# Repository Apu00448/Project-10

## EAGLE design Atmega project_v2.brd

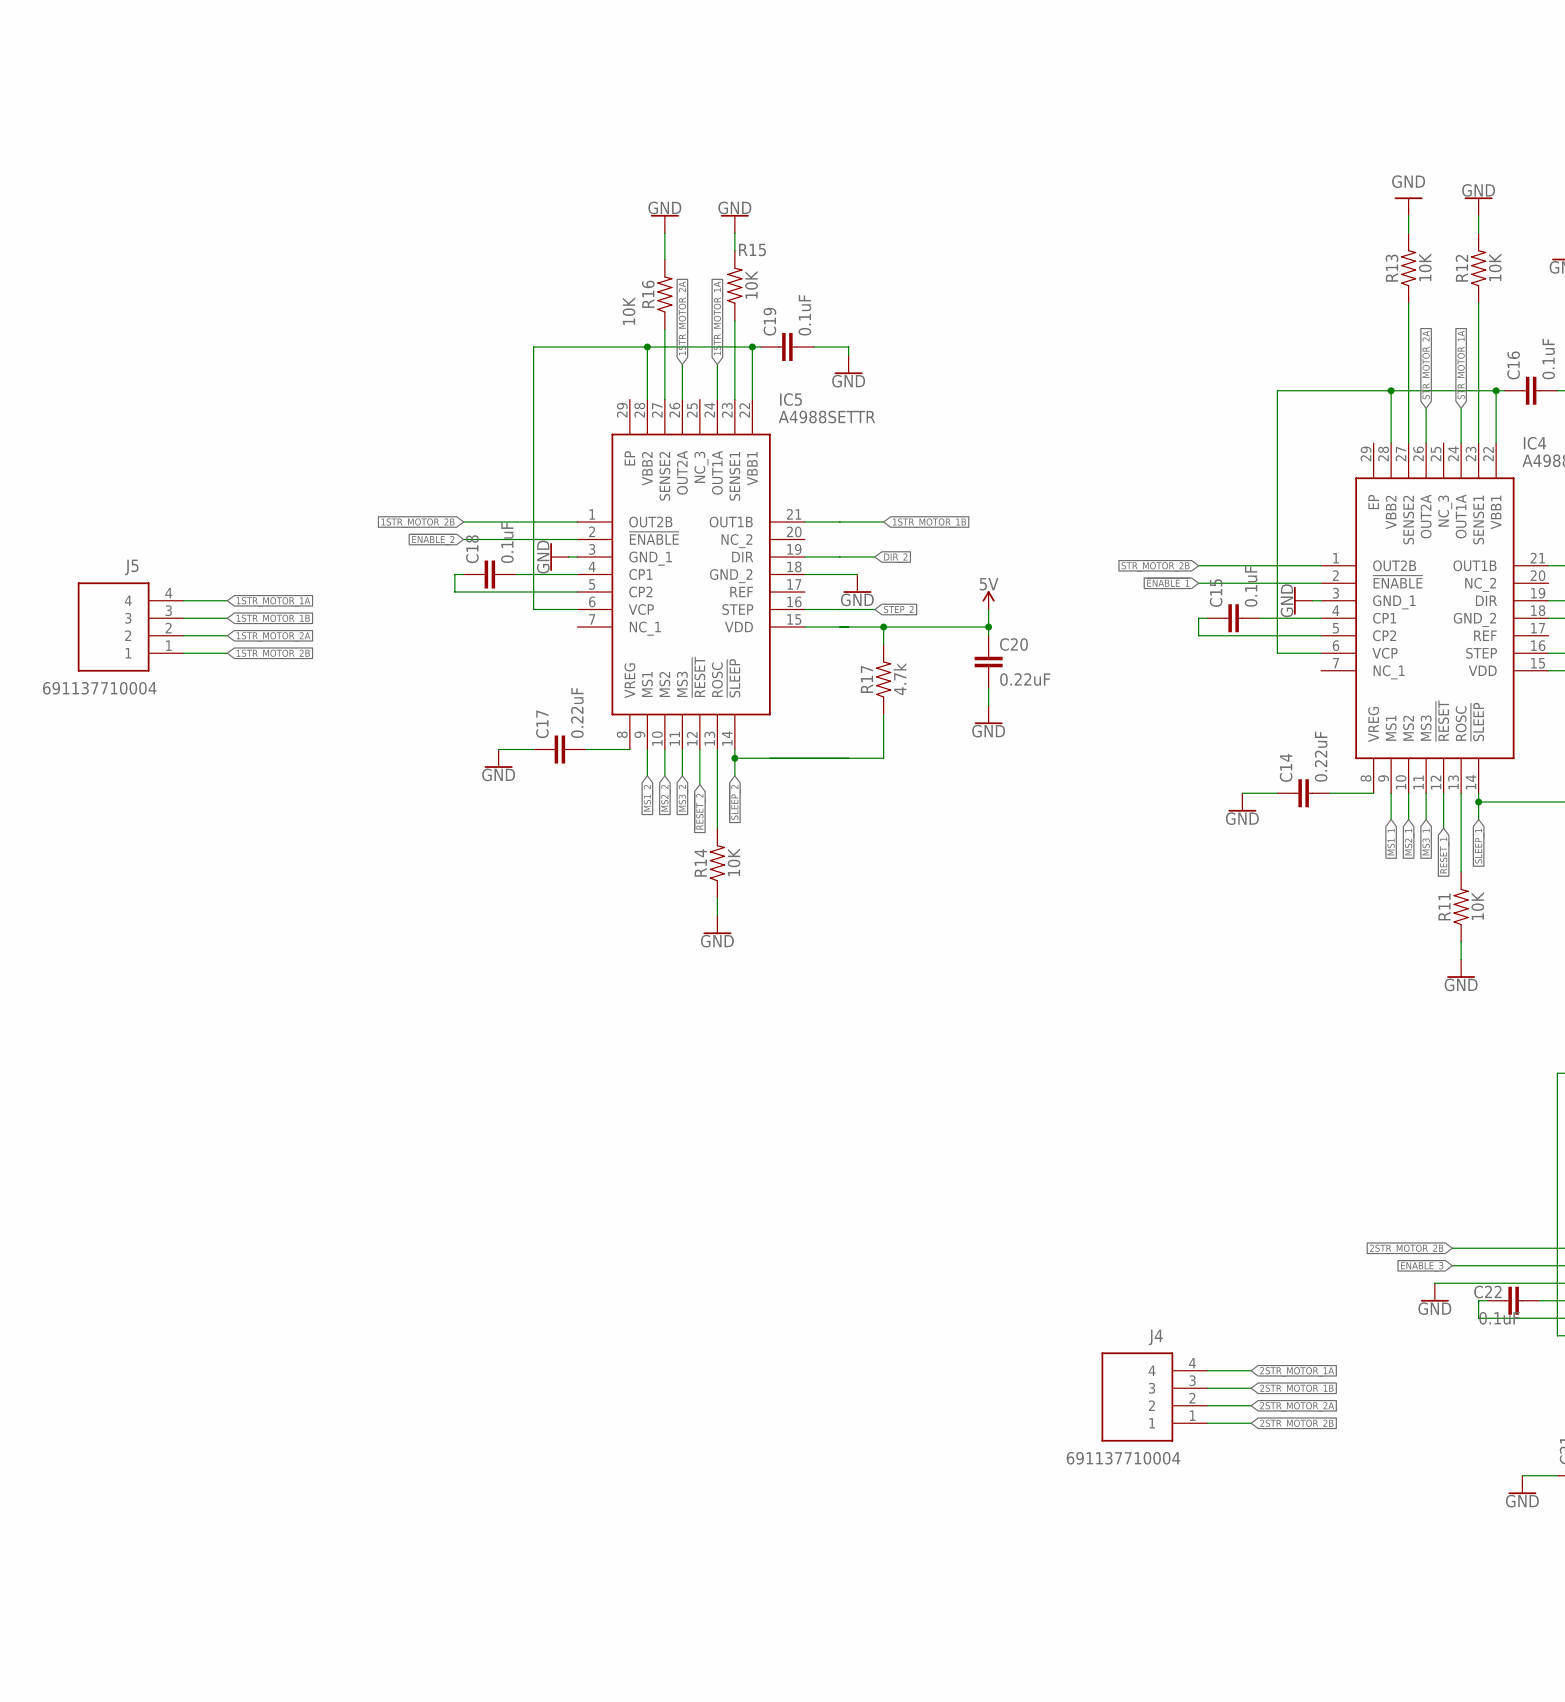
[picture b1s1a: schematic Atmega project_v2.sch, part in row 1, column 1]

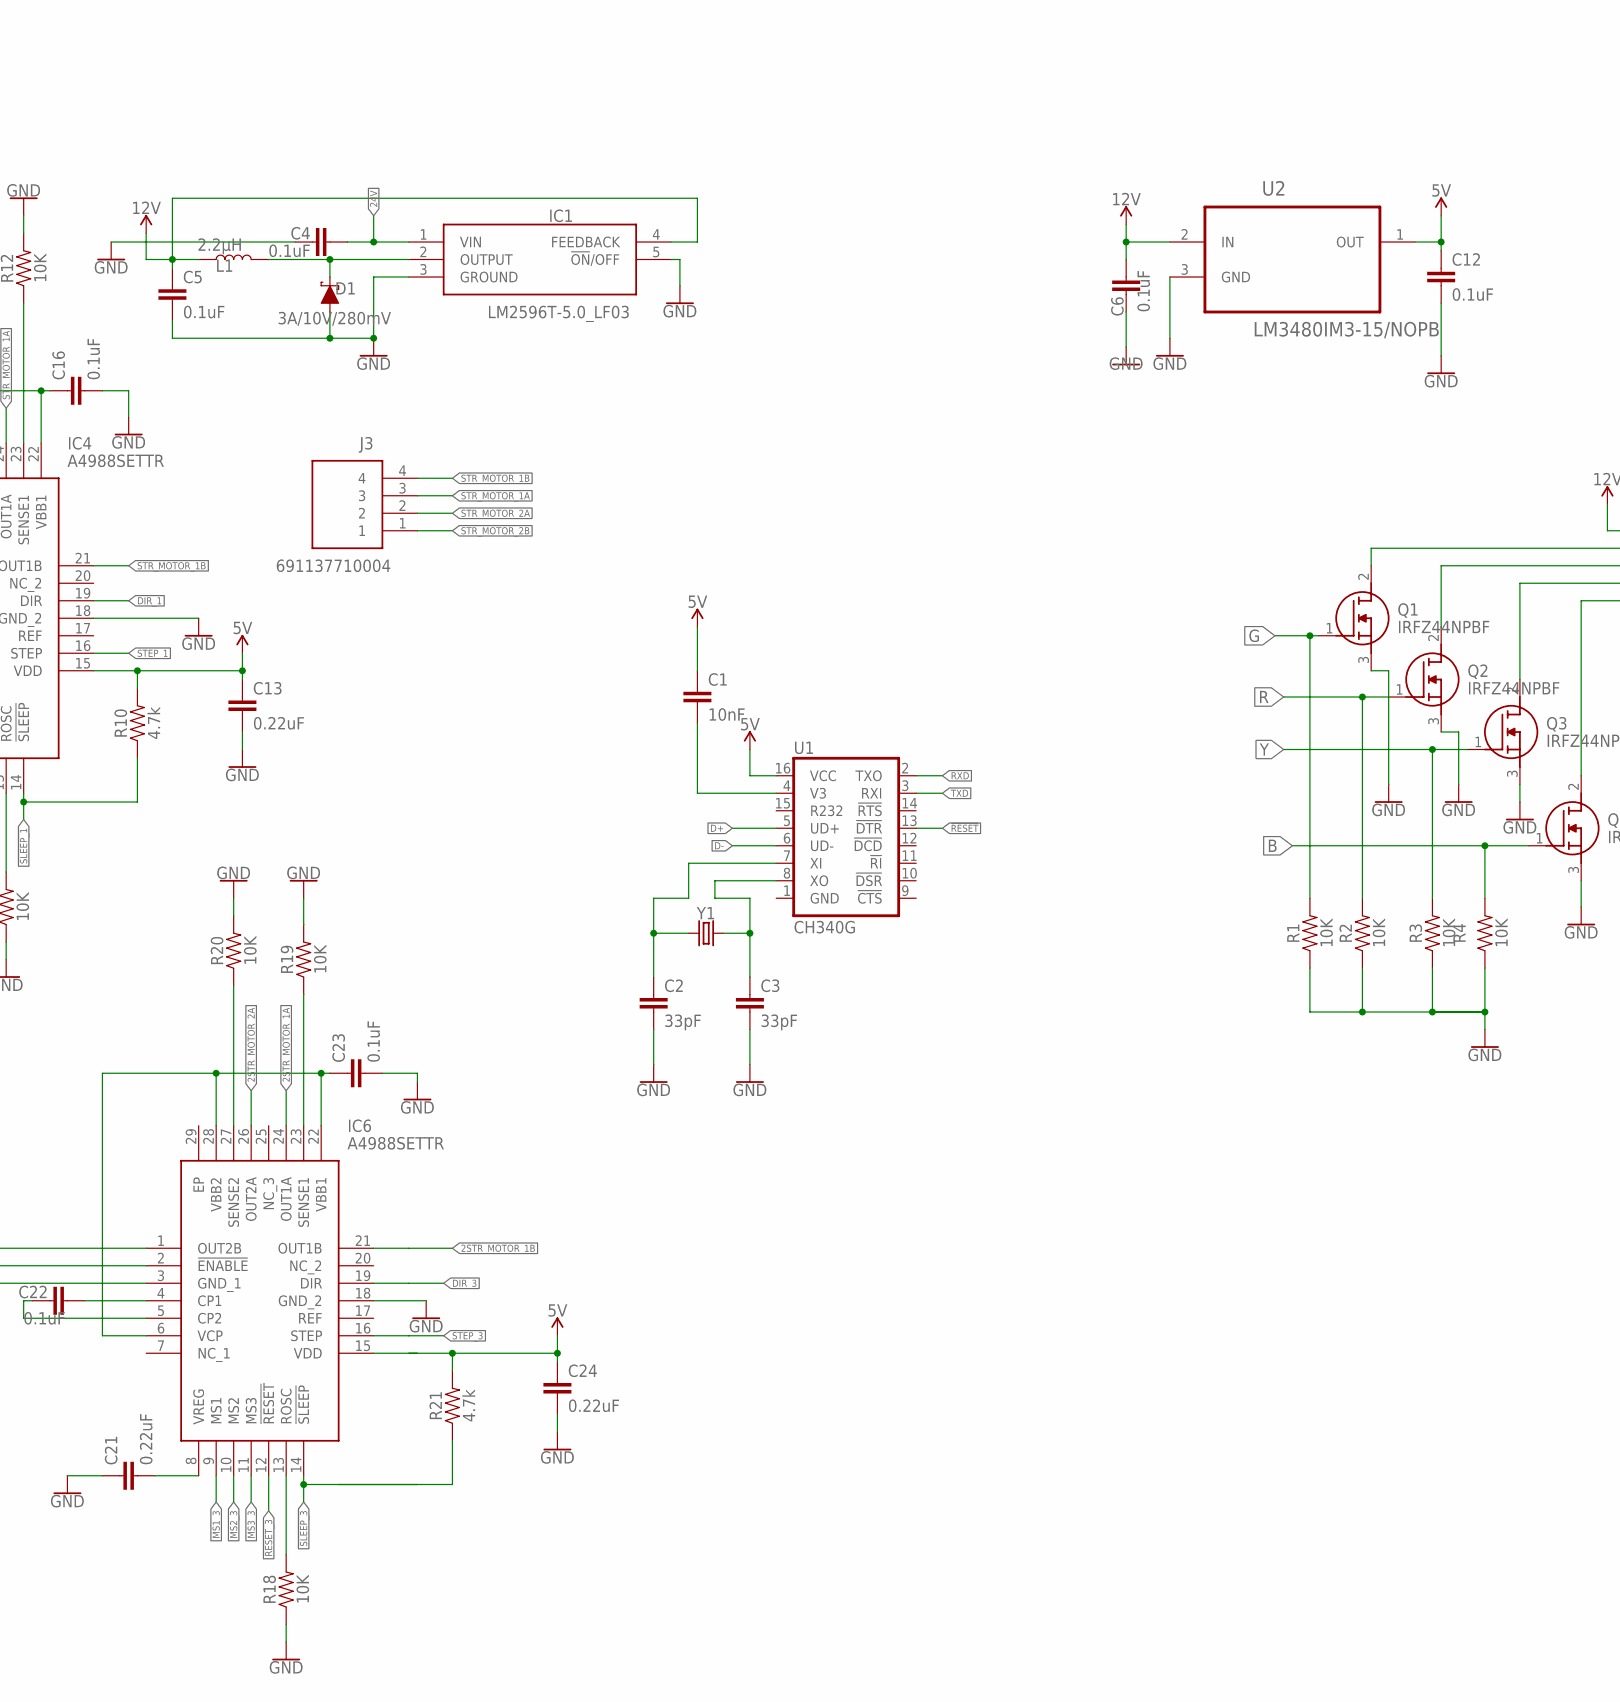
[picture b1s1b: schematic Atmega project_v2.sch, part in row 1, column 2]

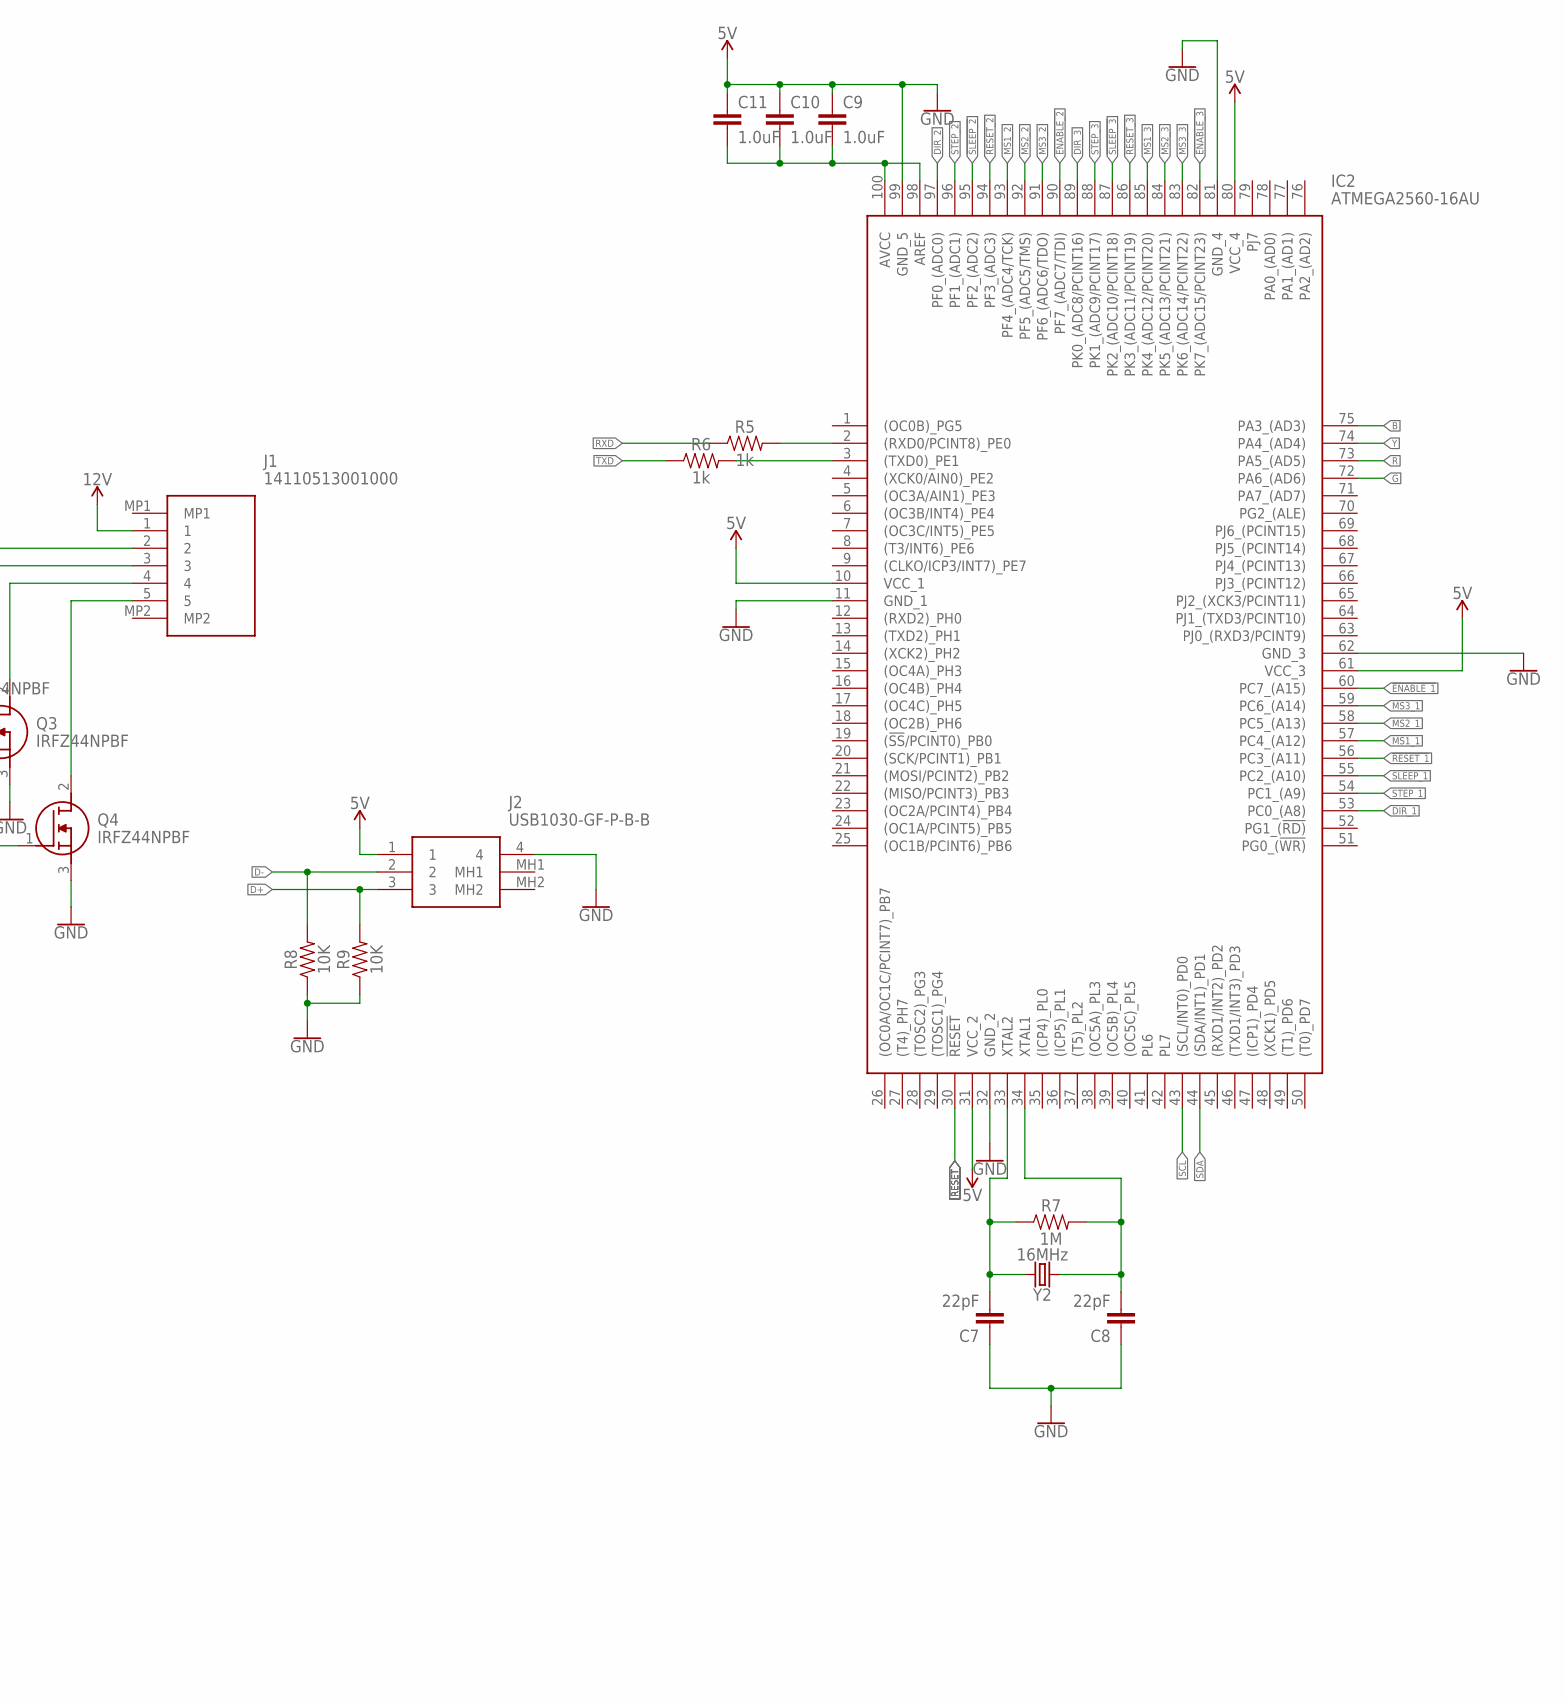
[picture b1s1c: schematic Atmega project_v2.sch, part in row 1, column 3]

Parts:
C1: 10nF; 0402-TIGHT
C2, C3: 33pF; 0402-TIGHT
C4: 0.1uF; 0603
C5, C6, C12, C15, C16, C18, C19, C22, C23: 0.1uF; 0402-TIGHT
C7, C8: 22pF; 0402-TIGHT
C9, C10, C11: 1.0uF; 0402-TIGHT
C13, C14, C17, C20, C21, C24: 0.22uF; 0402-TIGHT
D1: 3A/10V/280mV; SOD-323
IC1: LM2596T-5.0_LF03; TO170P470X1028X2142-5P
IC2: ATMEGA2560-16AU; QFP50P1600X1600X120-100N
IC4, IC5, IC6: A4988SETTR; QFN50P500X500X100-29N
J1: 14110513001000
J2: USB1030-GF-P-B-B; USB1030GFPBB
J3, J4, J5: 691137710004
L1: 2.2μH; 0805-WIDE
Q1, Q2, Q3, Q4: IRFZ44NPBF; TO254P483X1016X1994-3P
R1, R2, R3, R4, R8, R9, R11, R12, R13, R14, R15, R16, R18, R19, R20: 10K; 0402-TIGHT
R5, R6: 1k; 0402-TIGHT
R7: 1M; 0402-TIGHT
R10, R17, R21: 4.7k; 0402-TIGHT
U1: CH340G; SO016
U2: LM3480IM3-15/NOPB; SOT95P251X112-3N
Y1: CRYSTAL-12MHZ; CRYSTAL-SMD-2X2.5MM
Y2: 16MHz; CRYSTAL-SMD-5X3.2-4PAD

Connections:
1STR_MOTOR_1A: IC5.24 (OUT1A), J5.4
1STR_MOTOR_1B: J5.3
1STR_MOTOR_2A: IC5.26 (OUT2A), J5.2
1STR_MOTOR_2B: IC5.1 (OUT2B), J5.1
2STR_MOTOR_1A: IC6.24 (OUT1A), J4.4
2STR_MOTOR_1B: J4.3
2STR_MOTOR_2A: IC6.26 (OUT2A), J4.2
2STR_MOTOR_2B: IC6.1 (OUT2B), J4.1
5V: C1.1, C9.1, C10.1, C11.1, C12.1, C13.1, C20.1, C24.1, IC2.10 (VCC_1), IC2.31 (VCC_2), IC2.61 (VCC_3), IC2.80 (VCC_4), IC2.99 (GND_5), IC4.15 (VDD), J2.1, R10.2, R17.2, R21.2, U1.16 (VCC), U2.1 (OUT)
5V1: IC5.15 (VDD)
5V2: IC6.15 (VDD)
12V: C5.1, C6.2, IC1.4 (FEEDBACK), J1.1, L1.1, U2.2 (IN)
24V: C4.2, IC1.1 (VIN)
!ENABLE_1: IC2.60 (PC7_(A15)), IC4.2 (!ENABLE)
!ENABLE_2: IC2.90 (PF7_(ADC7/TDI)), IC5.2 (!ENABLE)
!ENABLE_3: IC2.82 (PK7_(ADC15/PCINT23)), IC6.2 (!ENABLE)
!RESET: IC2.30 (!RESET), U1.13 (!DTR)
!RESET_1: IC2.56 (PC3_(A11)), IC4.12 (!RESET)
!RESET_2: IC2.94 (PF3_(ADC3)), IC5.12 (!RESET)
!RESET_3: IC2.86 (PK3_(ADC11/PCINT19)), IC6.12 (!RESET)
!SLEEP_1: IC2.55 (PC2_(A10)), IC4.14 (!SLEEP), R10.1
!SLEEP_2: IC2.95 (PF2_(ADC2)), IC5.14 (!SLEEP), R17.1, R21.1
!SLEEP_3: IC2.87 (PK2_(ADC10/PCINT18)), IC6.14 (!SLEEP)
B: IC2.75 (PA3_(AD3)), Q4.1 (G), R4.2
D+: J2.3, R9.2, U1.5 (UD+)
D-: J2.2, R8.2, U1.6 (UD-)
DIR_1: IC2.53 (PC0_(A8)), IC4.19 (DIR)
DIR_2: IC2.97 (PF0_(ADC0)), IC5.19 (DIR), IC6.19 (DIR)
DIR_3: IC2.89 (PK0_(ADC8/PCINT16))
G: IC2.72 (PA6_(AD6)), Q1.1 (G), R1.2
GND: C2.2, C3.2, C4.1, C5.2, C6.1, C7.1, C8.1, C12.2, C13.2, C14.1, C16.2, C17.1, C19.2, C20.2, C21.1, C23.2, C24.2, D1.A, IC1.3 (GROUND), IC1.5 (!ON!/OFF), IC2.11 (GND_1), IC2.32 (GND_2), IC2.62 (GND_3), IC2.81 (GND_4), IC4.3 (GND_1), IC4.18 (GND_2), IC5.3 (GND_1), IC5.18 (GND_2), IC6.3 (GND_1), IC6.18 (GND_2), J2.4, Q1.3 (S), Q2.3 (S), Q3.3 (S), Q4.3 (S), R1.1, R2.1, R3.1, R4.1, R8.1, R9.1, R11.1, R12.2, R13.2, R14.1, R15.2, R16.2, R18.1, R19.2, R20.2, U2.3 (GND)
MS1_1: IC2.57 (PC4_(A12)), IC4.9 (MS1)
MS1_2: IC2.93 (PF4_(ADC4/TCK)), IC5.9 (MS1)
MS1_3: IC2.85 (PK4_(ADC12/PCINT20)), IC6.9 (MS1)
MS2_1: IC2.58 (PC5_(A13)), IC4.10 (MS2)
MS2_2: IC2.92 (PF5_(ADC5/TMS)), IC5.10 (MS2)
MS2_3: IC2.84 (PK5_(ADC13/PCINT21)), IC6.10 (MS2)
MS3_1: IC2.59 (PC6_(A14)), IC4.11 (MS3)
MS3_2: IC2.91 (PF6_(ADC6/TDO)), IC5.11 (MS3)
MS3_3: IC2.83 (PK6_(ADC14/PCINT22)), IC6.11 (MS3)
unnamed: C1.2, U1.4 (V3)
unnamed: J1.2, Q1.2 (D)
unnamed: J1.3, Q2.2 (D)
unnamed: J1.4, Q3.2 (D)
unnamed: J1.5, Q4.2 (D)
unnamed: C2.1, U1.7 (XI), Y1.P1 (1)
unnamed: C3.1, U1.8 (XO), Y1.P3 (2)
unnamed: C8.2, IC2.34 (XTAL1), R7.2, Y2.1
unnamed: C7.2, IC2.33 (XTAL2), R7.1, Y2.3 (2)
unnamed: C9.2, C10.2, C11.2, IC2.98 (AREF), IC2.100 (AVCC)
unnamed: C14.2, IC4.8 (VREG)
unnamed: C15.2, IC4.4 (CP1)
unnamed: IC4.13 (ROSC), R11.2
unnamed: C15.1, IC4.5 (CP2)
unnamed: C16.1, IC4.6 (VCP), IC4.22 (VBB1), IC4.28 (VBB2)
unnamed: D1.C, IC1.2 (OUTPUT), L1.2
unnamed: C21.2, IC6.8 (VREG)
unnamed: IC6.13 (ROSC), R18.2
unnamed: IC4.23 (SENSE1), R12.1
unnamed: IC4.27 (SENSE2), R13.1
unnamed: C22.2, IC6.4 (CP1)
unnamed: C22.1, IC6.5 (CP2)
unnamed: C17.2, IC5.8 (VREG)
unnamed: IC5.13 (ROSC), R14.2
unnamed: C18.2, IC5.4 (CP1)
unnamed: C18.1, IC5.5 (CP2)
unnamed: C19.1, IC5.6 (VCP), IC5.22 (VBB1), IC5.28 (VBB2)
unnamed: IC5.23 (SENSE1), R15.1
unnamed: IC5.27 (SENSE2), R16.1
unnamed: C23.1, IC6.6 (VCP), IC6.22 (VBB1), IC6.28 (VBB2)
unnamed: IC6.23 (SENSE1), R19.1
unnamed: IC6.27 (SENSE2), R20.1
R: IC2.73 (PA5_(AD5)), Q2.1 (G), R2.2
RXD: IC2.2 ((RXD0/PCINT8)_PE0), R5.1, R5.2, U1.2 (TXO)
SCL: IC2.43 ((SCL/INT0)_PD0)
SDA: IC2.44 ((SDA/INT1)_PD1)
STEP_1: IC2.54 (PC1_(A9)), IC4.16 (STEP)
STEP_2: IC2.96 (PF1_(ADC1)), IC5.16 (STEP), IC6.16 (STEP)
STEP_3: IC2.88 (PK1_(ADC9/PCINT17))
STR_MOTOR_1A: IC4.24 (OUT1A), J3.3
STR_MOTOR_1B: IC4.21 (OUT1B), J3.4
STR_MOTOR_1B1: IC5.21 (OUT1B)
STR_MOTOR_1B2: IC6.21 (OUT1B)
STR_MOTOR_2A: IC4.26 (OUT2A), J3.2
STR_MOTOR_2B: IC4.1 (OUT2B), J3.1
TXD: IC2.3 ((TXD0)_PE1), R6.1, R6.2, U1.3 (RXI)
Y: IC2.74 (PA4_(AD4)), Q3.1 (G), R3.2

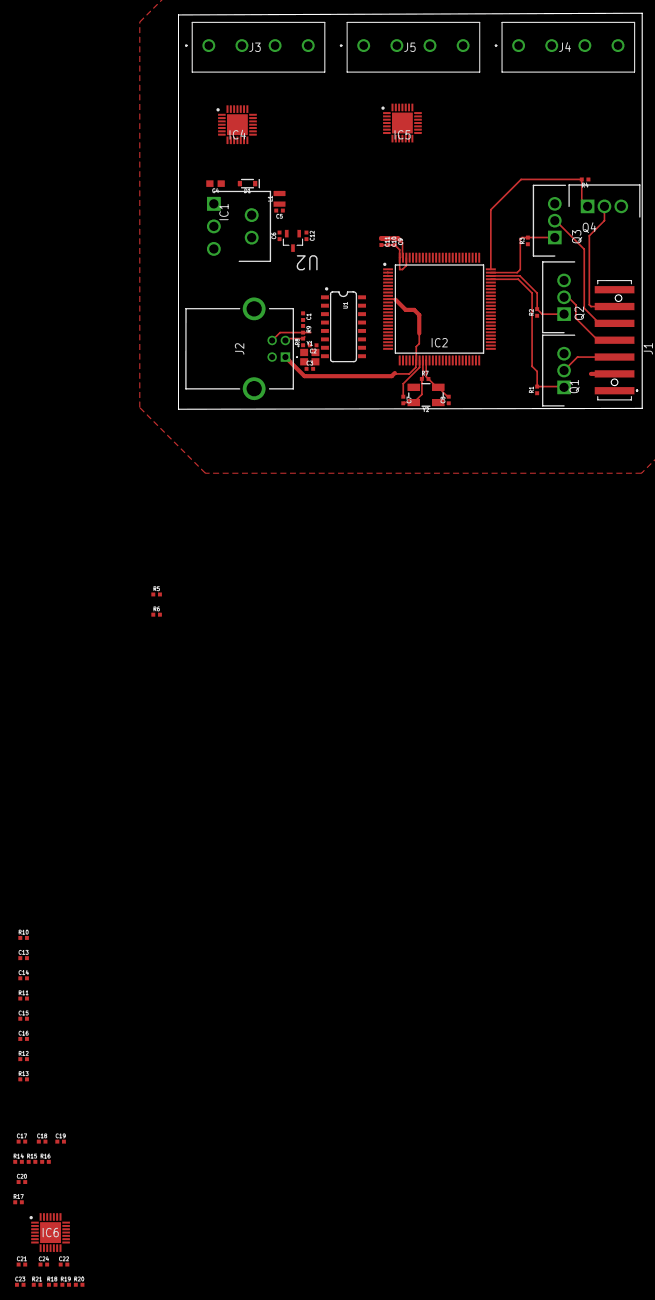
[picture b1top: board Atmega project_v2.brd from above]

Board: 2 copper layers, 70.0 x 59.7 mm, 65 parts (0 on the bottom side), 77 nets.

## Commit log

2024-01-03 ATMega Project-- Eagle

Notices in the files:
parts and their libraries:
SparkFun-Capacitors: Licensing: Creative Commons ShareAlike 4.0 International - https://creativecommons.org/licenses/by-sa/4.0
